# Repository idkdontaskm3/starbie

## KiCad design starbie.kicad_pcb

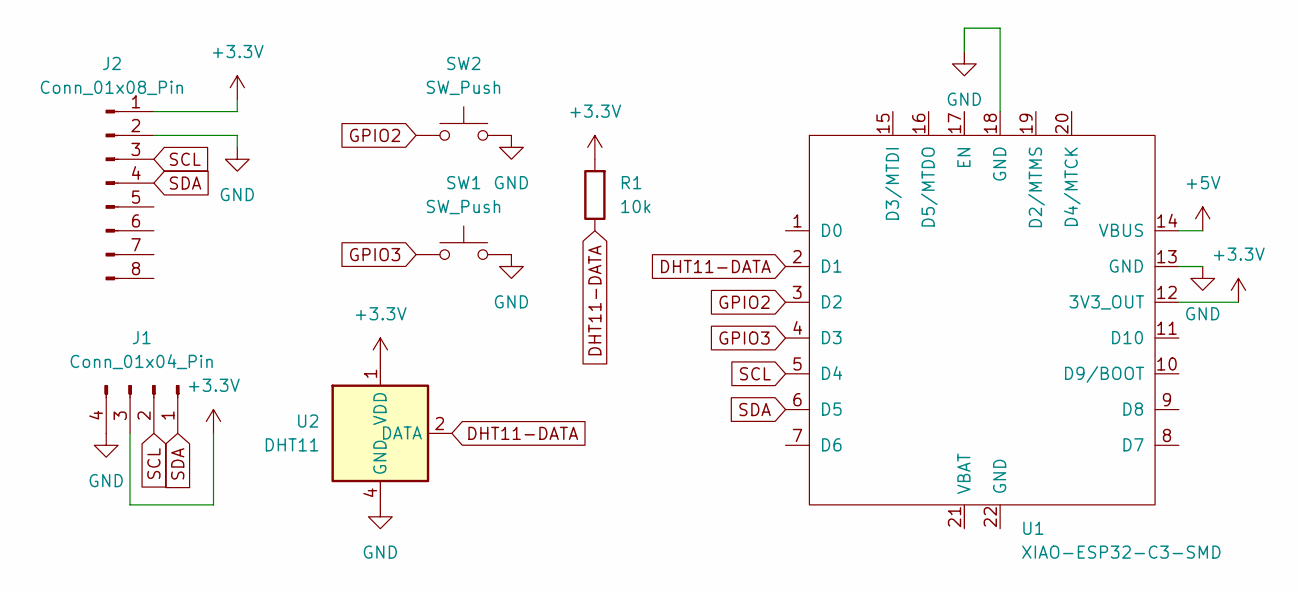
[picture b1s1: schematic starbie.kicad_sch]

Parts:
J1: Conn_01x04_Pin; Display_128x64_096_I2C
J2: Conn_01x08_Pin; PinHeader_1x08_P2.54mm_Vertical
R1: 10k; R_Axial_DIN0204_L3.6mm_D1.6mm_P7.62mm_Horizontal
SW1, SW2: SW_Push; SW_Cherry_MX_1.00u_PCB
U1: XIAO-ESP32-C3-SMD; MCU_Seeed_ESP32C3
U2: DHT11; Aosong_DHT11_5.5x12.0_P2.54mm

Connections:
+3.3V: J1.3, J2.1, R1.2, U1.12 (3V3_OUT), U2.1 (VDD)
+5V: U1.14 (VBUS)
DHT11-DATA: R1.1, U1.2 (D1), U2.2 (DATA)
GND: J1.4, J2.2, SW1.2, SW2.2, U1.13 (GND), U1.18 (GND), U2.4 (GND)
GPIO2: SW2.1, U1.3 (D2)
GPIO3: SW1.1, U1.4 (D3)
SCL: J1.2, J2.3, U1.5 (D4)
SDA: J1.1, J2.4, U1.6 (D5)

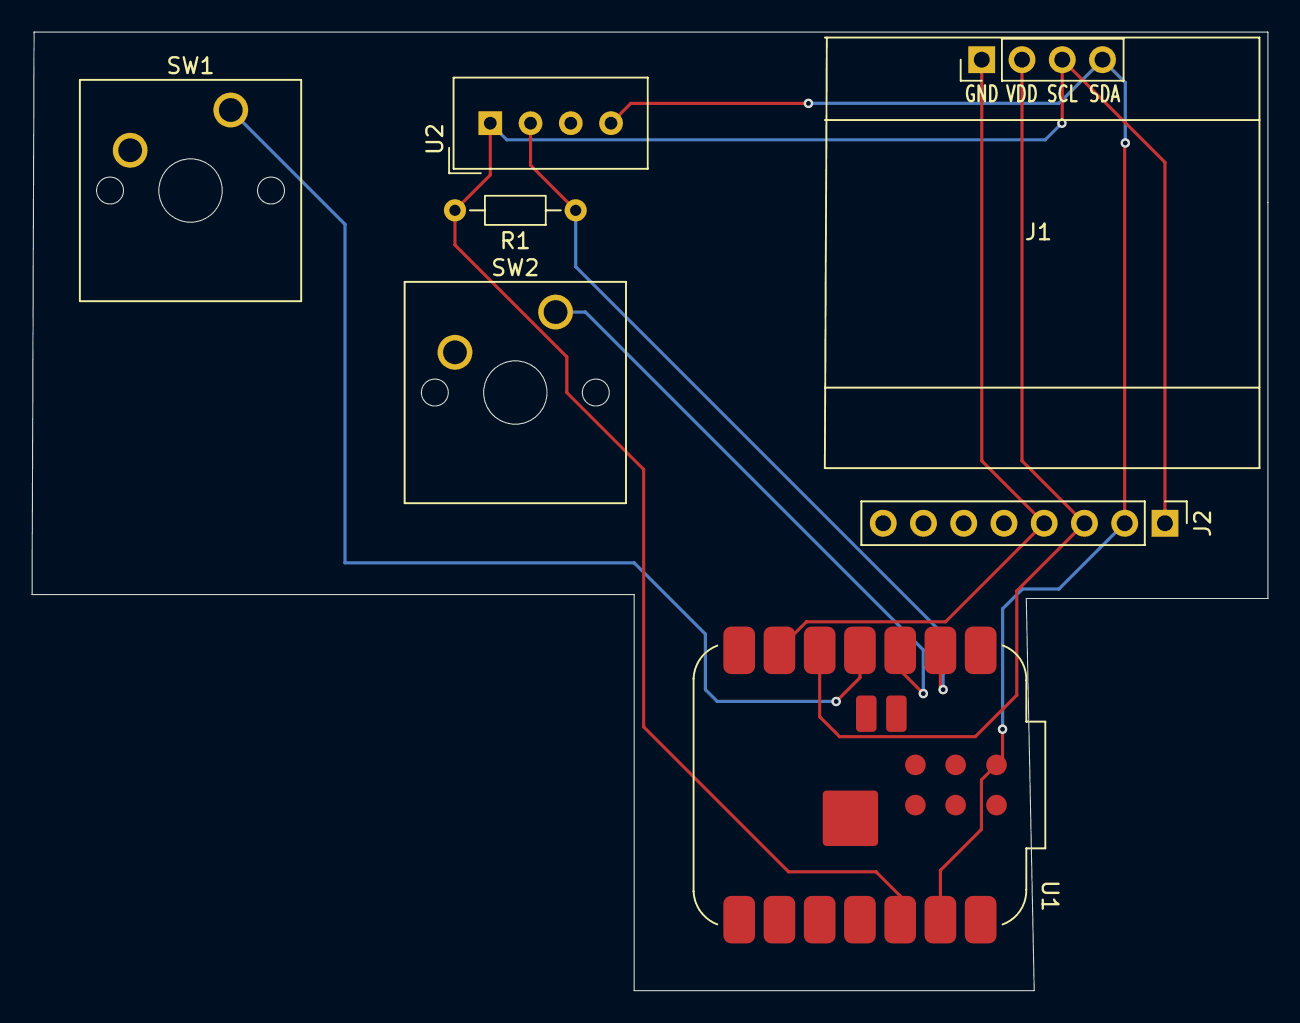
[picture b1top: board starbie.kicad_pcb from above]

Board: 2 copper layers, 78.0 x 60.5 mm, 7 parts (0 on the bottom side), 7 nets.
